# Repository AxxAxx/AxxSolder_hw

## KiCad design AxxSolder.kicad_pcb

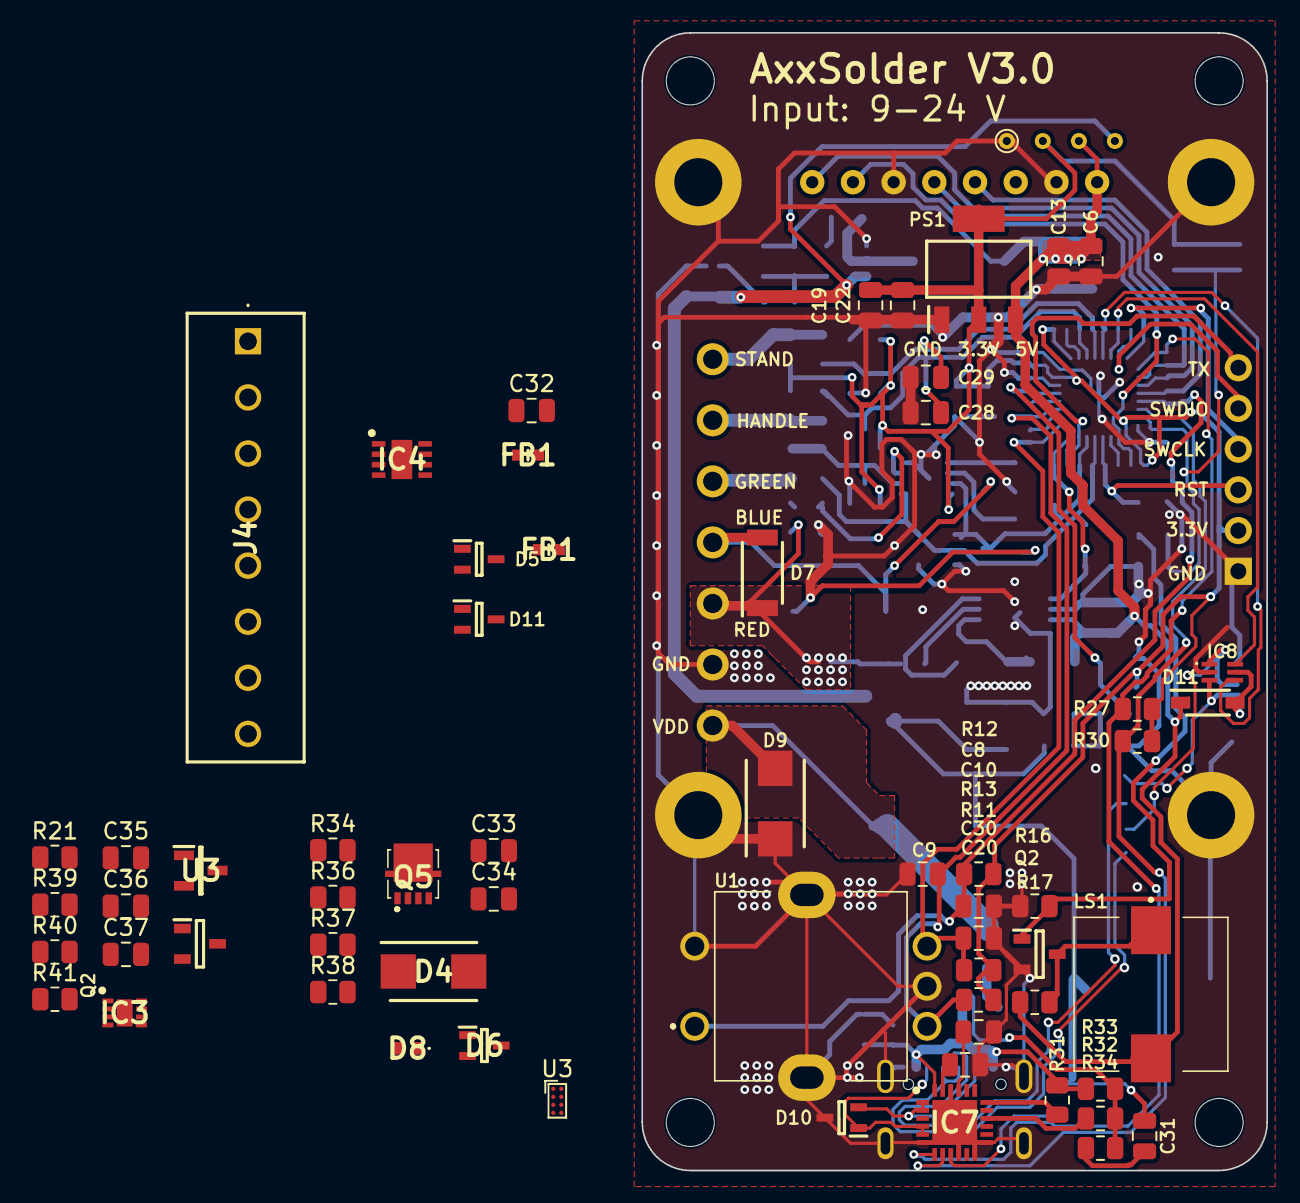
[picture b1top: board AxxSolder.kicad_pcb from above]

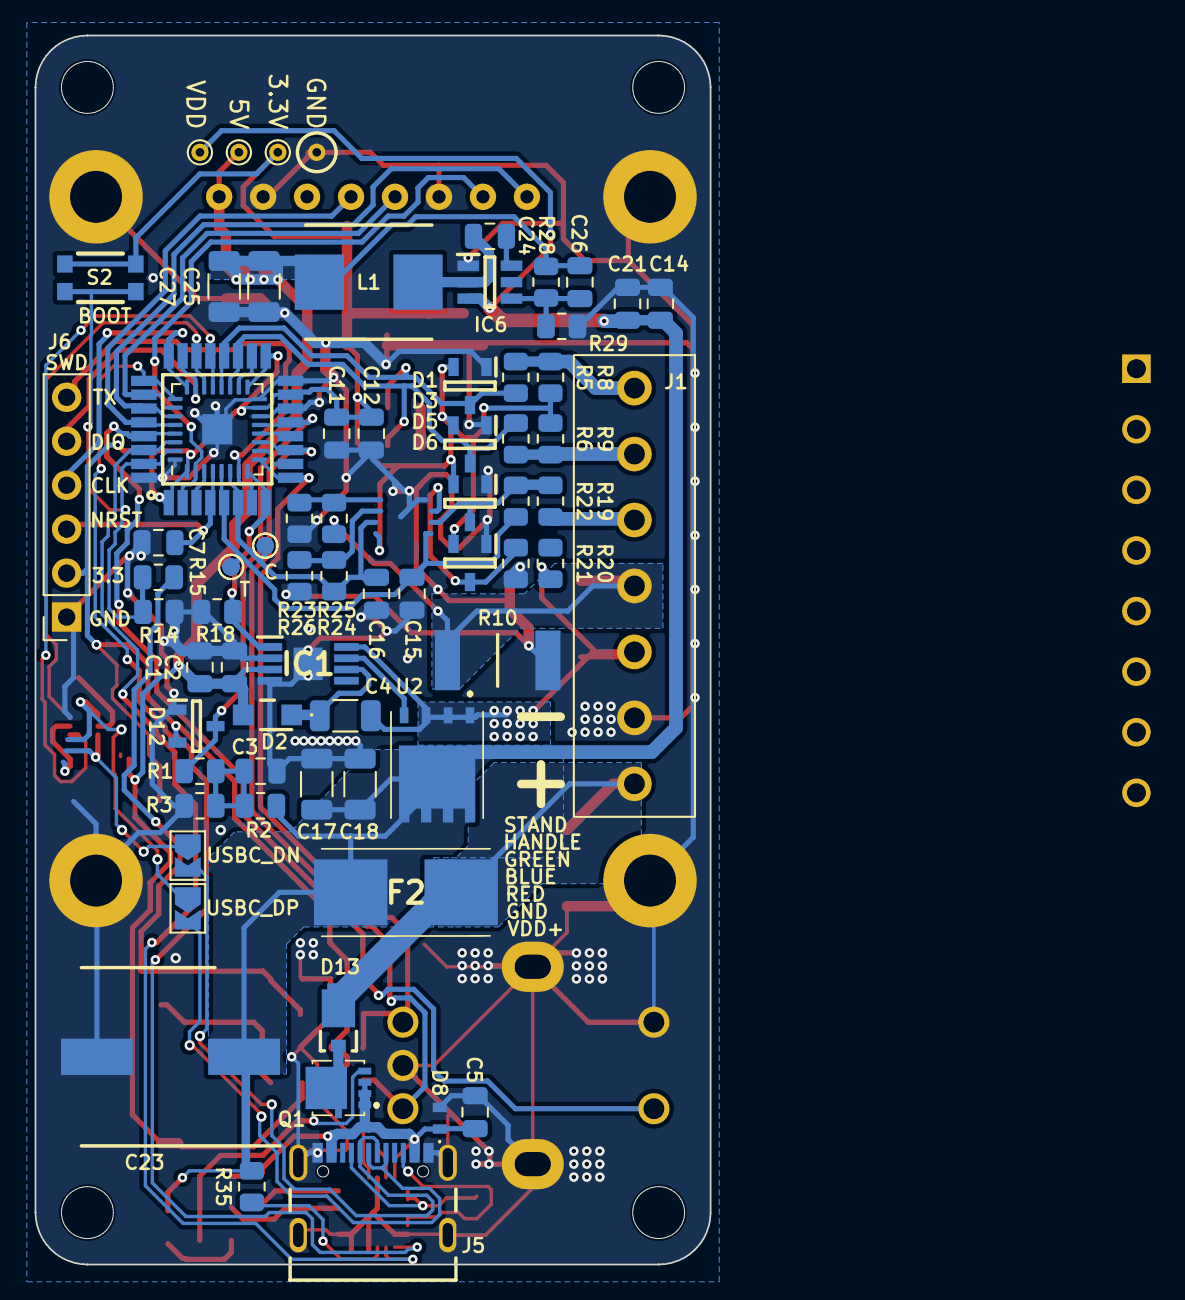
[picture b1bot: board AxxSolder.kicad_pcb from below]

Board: 2 copper layers, 39.0 x 71.0 mm, 137 parts (71 on the bottom side), 70 nets.

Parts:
C1, C6, C12, C14, C19, C32: 10u; C_0805_2012Metric
C2, C3, C7, C8, C9, C10, C11, C13, C21, C22, C24, C28, C29, C31, C34, C35, C36, C37: 100n; C_0805_2012Metric
C4, C25, C27: 22u; C_1206_3216Metric
C5: 4.7u; C_0805_2012Metric
C15, C16: 1n; C_0805_2012Metric
C17, C18: 22u/35V; C_1206_3216Metric
C20, C30, C33: 1u; C_0805_2012Metric
C23: 330u; CAPAE1030X1050N
C26: 75p; C_0805_2012Metric
D1, D3, D5#2, D6#2, D12: BAT54S; SOT95P230X110-3N
D2: PMEG6020ER; PMEG6020ER115
D4: SMBJ24A; DIOM5436X261N
D4#2: Waveshare 1.5inch OLED Module; 1_5inch-rgb-oled-module_asm-1110
D5, D11: BAV199WQ-7; SOT65P210X110-3N
D6, D10: ESDA25W; SOT65P210X110-3N
D7: PMEG10030ELPX; SODFL4725X110N
D8: ESDA25P35; ESDA25P351U1M
D8#2: ESDA25P35-1U1M; ESDA25P351U1M
D9: SMBJ24CA; DIOM5436X261N
D11#2: 1N5819HW-7-F; SOD3716X145N
D13: V7NM103-M3_I; V7NM103M3I
F2: 0154007.DRL; 0154100DR
FB1, FB1#2: BLM18HE601SN1D; BLM18SP221SN1B
H1, H2, H3, H4: MountingHole; MountingHole_3mm
IC1: LTC4440AHMS8E; SOP65P490X110-9N
IC2: STM32G431KBT6; QFP80P900X900X160-32N
IC3: OPA2387DSGT; SON50P200X200X80-9N
IC4: OPA2387DSGT; SON65P300X300X100-9N-D
IC5: STM32G431KBT6; UFQFPN-32-1EP_5x5mm_P0.5mm_EP3.5x3.5mm
IC6: TPS54302DDCR; SOT95P280X110-6N
IC7: STUSB4500QTR; QFN50P400X400X100-25N-D
IC8: USBLC6-2P6; USBLC62P6
J1: Conn_01x07_Male; 691243310007
J4: 691243110008
J5: USB4105-GF-A-120; GCT_USB4105-GF-A-120
J6: Conn_01x06_Socket; PinSocket_1x06_P2.54mm_Vertical
JP1, JP2: SolderJumper_2_Open; SolderJumper-2_P1.3mm_Open_TrianglePad1.0x1.5mm
L1: SRP7028CC; INDPM7366X300N
LS1: CMI-9653S-SMT-TR; CMI9653SSMTTR
PS1: LD1117AS33TR; SOT230P700X190-4N
Q1, Q5: STL9P3LLH6; STL20N6F7
Q2, Q2#2: 2N7002NXAKR; SOT95P230X110-3N
R1, R5, R6, R17, R25, R26, R27, R30, R37: 4k7; R_0805_2012Metric
R2: 47k; R_0805_2012Metric
R3: 6k8; R_0805_2012Metric
R8, R9, R11, R12, R13, R14, R16, R18, R21, R34#2, R40, R41: 10k; R_0805_2012Metric
R10: 2m; RESC6432X89N
R15: 220; R_0805_2012Metric
R19, R20: 1k5; R_0805_2012Metric
R21#2, R22, R39: 360k; R_0805_2012Metric
R23, R24: 220k; R_0805_2012Metric
R28: 100k; R_0805_2012Metric
R29: 13k3; R_0805_2012Metric
R31, R35, R36: 1k; R_0805_2012Metric
R32, R34, R38: 22k; R_0805_2012Metric
R33: 100; R_0805_2012Metric
S2: KMR211G_LFS; KMR_2
TP3: GND_TP; TestPoint_THTPad_D1.0mm_Drill0.5mm
TP5: TC_TP; TestPoint_Pad_D1.0mm
TP5#2: Thermocouple_TP; TestPoint_Pad_D1.0mm
TP6, TP6#2: Current_TP; TestPoint_Pad_D1.0mm
TP7: 5V_TP; TestPoint_THTPad_D1.0mm_Drill0.5mm
TP8: VDD_TP; TestPoint_THTPad_D1.0mm_Drill0.5mm
TP9: 3.3V_TP; TestPoint_THTPad_D1.0mm_Drill0.5mm
U1: PEC11L-4220F-S0015; PEC11L4220FS0015
U2: BSC014N04LS
U3: TPD2E2U06QDBZRQ1; SOT95P237X95-3N
U3#2: OPA2376xxYZD; Texas_DSBGA-8_0.9x1.9mm_Layout2x4_P0.5mm

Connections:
+3.3V: C19.1, C22.1, D1.2 (K), D3.2 (K), D5.2, D5#2.2 (K), D6#2.2 (K), D11.2, D12.2 (K), FB1.2, IC2.1 (VDD_1), IC2.17 (VDD_2), IC3.8 (V+), IC4.8 (V+), IC5.1 (VDD_1), IC5.17 (VDD_2), J6.2, PS1.2 (VOUT_1), PS1.4 (VOUT_2), R8.1, R9.1, R11.2, R12.1, R13.1, R21.1, R27.2, R30.2, R34#2.1, R40.1, R41.1, S2.1, TP9.1
+5V: C1.1, C2.1, C6.2, C13.2, C25.2, C26.2, C27.2, C32.2, D2.2, D4#2.1 (VCC), D11#2.1, IC1.3 (VCC), IC8.5 (VBUS), L1.2, LS1.2 (+), PS1.3 (VIN), R17.1, R28.1, TP7.1
/BLUE: D7.2, J1.4, J4.5, R10.1, R25.1
/Buzzer: IC2.31 (PB8-BOOT0), IC5.31 (PB8-BOOT0), R14.2, R15.1, S2.2
/CC1: D6.2, IC7.1 (CC1DB), IC7.2 (CC1)
/CC2: D6.1, IC7.4 (CC2), IC7.5 (CC2DB)
/Current: C16.1, IC2.6 (PA1), IC3.7, IC5.6 (PA1), R24.1, TP6#2.1
/Current_1: IC4.7 (OUT_B), TP6.1
/ENC_A: C10.1, IC2.9 (PA4), IC5.9 (PA4), R13.2, U1.5
/ENC_B: C9.1, IC2.11 (PA6), IC5.11 (PA6), R11.1, U1.3
/GREEN: J1.3, J4.4, R19.1
/Handle_inp1: IC2.19 (PA9), IC5.19 (PA9), R37.1
/Handle_inp2: D3.3 (common), IC2.18 (PA8), IC5.18 (PA8), R6.1
/Handle_sense1: C34.1, J4.3, R34#2.2, R37.2
/Handle_sense2: C28.1, J4.2, R6.2, R9.2
/Heater: IC1.1 (INP), IC2.8 (PA3), IC5.8 (PA3), R18.1
/NRST: C7.2, IC2.4 (PG10-NRST), IC5.4 (PG10-NRST), J6.3
/RED: C4.1, D7.1, IC1.8 (TS), J1.5, J4.6, R20.1, U2.1 (S)
/SCL: IC2.25 (PA15), IC5.25 (PA15), IC7.7 (SCL), R30.1
/SDA: IC2.30 (PB7), IC5.30 (PB7), IC7.8 (SDA), R27.1
/SD_CS: IC2.3 (PF1-OSC_OUT), IC5.3 (PF1-OSC_OUT)
/SPI_CS: D4#2.6 (CS), IC2.29 (PB6), IC5.29 (PB6)
/SPI_DC: D4#2.7 (DC), IC2.2 (PF0-OSC_IN), IC5.2 (PF0-OSC_IN)
/SPI_MOSI: D4#2.4 (DIN), IC2.28 (PB5), IC5.28 (PB5)
/SPI_RST: D4#2.8 (RST), IC2.27 (PB4), IC5.27 (PB4)
/SPI_SCK: D4#2.5 (CLK), IC2.26 (PB3), IC5.26 (PB3)
/SW1: C8.1, C35.1, IC2.10 (PA5), IC5.10 (PA5), R12.2, R41.2, U1.1
/SW2: C36.1, R40.2
/SW3: C37.1, R21.2
/SWCLK: IC2.24 (PA14), IC5.24 (PA14), J6.4
/SWDIO: IC2.23 (PA13), IC5.23 (PA13), J6.5
/SW_2: IC2.7 (PA2), IC5.7 (PA2)
/SW_3: IC2.12 (PA7), IC5.12 (PA7)
/Stand_inp: D1.3 (common), IC2.20 (PA10), IC5.20 (PA10), R5.1
/Stand_sense: C29.1, J1.1, J4.1, R5.2, R8.2
/TC: C15.1, IC2.5 (PA0), IC3.1, IC5.5 (PA0), R22.1, TP5.1
/Thermocouple_1: IC4.1 (OUT_A), TP5#2.1
/USB_D+: IC2.22 (PA12), IC5.22 (PA12), IC8.6 (I/O1_2), U3.1 (IO1)
/USB_D-: IC2.21 (PA11), IC5.21 (PA11), IC8.4 (I/O2_2), U3.2 (IO2)
/USB_DN: IC8.3 (I/O2_1), J5.A7 (DN1), J5.B7 (DN2), JP2.1 (A)
/USB_DP: IC8.1 (I/O1_1), J5.A6 (DP1), J5.B6 (DP2), JP1.1 (A)
/USB_PD_GATE: Q1.4 (G), R34.1
/VBUS: C5.2, C20.1, D8.1 (K), D8#2.1 (K), IC7.24 (VDD), J5.A4_B9 (VBUS), J5.B4_A9 (VBUS), Q1.1 (S_1), Q1.2 (S_2), Q1.3 (S_3), Q5.1 (S), R31.2, R36.1, R38.2
/VDD_IN: C31.2, D9.2, D13.1 (K), F2.2, J1.7, J4.8, Q1.5 (D), Q5.5 (D), R35.1
/VDD_inp: D12.3 (common), IC2.13 (PB0), IC5.13 (PB0), R1.2
GND: C1.2, C2.2, C3.2, C5.1, C6.1, C7.1, C8.2, C9.2, C10.2, C11.2, C12.2, C13.1, C14.1, C15.2, C16.2, C17.2, C18.2, C19.2, C20.2, C21.1, C22.2, C23.2, C25.1, C27.1, C28.2, C29.2, C30.2, C32.1, C33.2, C34.2, C35.2, C36.2, C37.2, D1.1 (A), D3.1 (A), D4.2 (A), D4#2.2 (GND), D5.1, D5#2.1 (A), D6.3, D6#2.1 (A), D8.2 (A), D8#2.2 (A), D9.1, D10.3 (ANODE), D11.1, D12.1 (A), IC1.2 (GND_1), IC1.4 (GND_2), IC1.9 (EP), IC2.14 (VSSA), IC2.16 (VSS_1), IC2.32 (VSS_2), IC3.4 (V-), IC3.9 (THERMAL_PAD), IC4.4 (V-), IC4.9 (EP), IC5.14 (VSSA), IC5.16 (VSS_1), IC5.32 (VSS_2), IC6.1 (GND), IC7.6 (RESET), IC7.10 (GND), IC7.12 (ADDR0), IC7.13 (ADDR1), IC7.22 (VSYS), IC7.25 (EP), IC8.2 (GND), J1.6, J4.7, J5.A1_B12 (GND), J5.B1_A12 (GND), J5.S1 (SHELL_GND), J5.S2 (SHELL_GND), J5.S3 (SHELL_GND), J5.S4 (SHELL_GND), J6.1, PS1.1 (ADJ/GND), Q2.2, Q2#2.2 (S), R3.2, R10.2, R14.1, R16.2, R18.2, R21#2.2, R23.2, R26.2, R29.2, R39.2, TP3.1, U1.2, U1.4, U3.3 (GND)
unnamed: C3.1, R1.1, R2.2, R3.1
unnamed: C31.1, R33.2, R34.2
unnamed: D10.1 (CATHODE_1), J5.B5 (CC2)
unnamed: D10.2 (CATHODE_2), J5.A5 (CC1)
unnamed: C4.2, D2.1, IC1.6 (BOOST)
unnamed: IC1.7 (TG), U2.9 (G)
unnamed: C11.1, C12.1, FB1.1, IC2.15 (VDDA), IC5.15 (VDDA)
unnamed: D11.3, IC3.3 (+), R20.2, R39.1
unnamed: D5.3, IC3.2 (-), R19.2, R22.2
unnamed: IC3.5 (+), R23.1, R25.2
unnamed: IC3.6 (-), R24.2, R26.1
unnamed: IC4.3 (+IN_A), R21#2.1
unnamed: C24.1, IC6.6 (BOOT)
unnamed: C26.1, IC6.4 (FB), R28.2, R29.1
unnamed: C24.2, IC6.2 (SW), L1.1
unnamed: IC7.9 (DISCH), R35.2
unnamed: IC7.16 (VBUS_EN_SNK), R32.1
unnamed: IC7.18 (VBUS_VS_DISCH), R31.1, R36.2
unnamed: C33.1, IC7.21 (VREG_1V2)
unnamed: C30.1, IC7.23 (VREG_2V7)
unnamed: LS1.1 (-), Q2.3, Q2#2.3 (D), R17.2
unnamed: Q2#2.1 (G), R15.2, R16.1
unnamed: Q5.4 (G), R32.2, R33.1, R38.1
VDD: C14.2, C17.1, C18.1, C21.2, C23.1, D4.1 (K), F2.1, IC6.3 (VIN), R2.1, TP8.1, U2.10 (D)

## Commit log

2023-12-07 update filestructure for AxxSolder V3.0 and forward
2023-12-07 Add a submodule and python scripts
2023-12-22 multiple updates for AxxSolder hw 3.0
2023-12-23 update BOM
